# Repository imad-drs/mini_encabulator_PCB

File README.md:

# Mini Encabulator - PCB Design Project

A complete PCB design exercise demonstrating schematic capture, component selection, and board layout using KiCAD. This project implements a simple LED blinker with user-controllable blink rate.

*Final PCB layout with component placement and routing*

## 📋 Project Overview

The Mini Encabulator is a microcontroller-based device that:
- **Blinks an LED** when a button is pressed
- **Controls blink rate** via potentiometer position
- Demonstrates **complete PCB design workflow** from schematic to manufacturing files

This project was designed as a learning exercise for PCB design fundamentals, including proper power delivery, signal conditioning, and mechanical integration with an enclosure.

## 🎯 Features

- **Microcontroller-based control** using ATTiny85
- **Hardware debouncing** for reliable button input
- **Analog input** from potentiometer for variable timing
- **Regulated 5V power supply** from 7-12V input
- **In-circuit programming** via ISP header
- **Enclosure-ready design** with precise mounting holes
- **Two-layer PCB** with ground planes for noise immunity

## 🔧 Hardware Components

### Main Components

| Component | Part Number | Package | Purpose | Quantity |
|-----------|-------------|---------|---------|----------|
| Microcontroller | ATTiny85-20S | SOIC-8 | Main processor | 1 |
| Voltage Regulator | LM1117MP-5.0 | SOT-223 | 5V power supply | 1 |
| Protection Diode | MBR0520 | SOD-123 | Reverse current protection | 1 |

### Passive Components

| Component | Value | Package | Purpose | Quantity |
|-----------|-------|---------|---------|----------|
| Resistor | 10kΩ | 0805 | RESET pull-up | 1 |
| Resistor | 10kΩ | 0805 | Button debounce | 1 |
| Resistor | 1kΩ | 0805 | LED current limit | 1 |
| Capacitor | 1µF | 0805 | Power decoupling | 1 |
| Capacitor | 1µF | 0805 | Button debounce | 1 |

### Connectors

| Connector | Type | Pitch | Purpose | Quantity |
|-----------|------|-------|---------|----------|
| Power Input | Molex KK-254 2-pin | 2.54mm | External power | 1 |
| Button | Molex KK-254 2-pin | 2.54mm | User input | 1 |
| LED | Molex KK-254 2-pin | 2.54mm | Indicator output | 1 |
| Potentiometer | Molex KK-254 3-pin | 2.54mm | Analog input | 1 |
| ISP Header | IDC 2x3 | 2.54mm | Programming interface | 1 |

### Mechanical

- **Mounting Holes**: 4× M3 (3.2mm diameter)
- **Potential Compatible Enclosure**: Polycase SN25 or similar

## 📐 Technical Specifications

### Electrical Characteristics

- **Input Voltage**: 7-12V DC
- **Regulated Output**: 5V @ 800mA max (LM1117)
- **Microcontroller**: 20MHz max, 8KB Flash, 512B SRAM
- **Power Consumption**: ~50mA typical
- **LED Current**: 4mA @ 5V with 1kΩ resistor

### Design Rules

- **Minimum Trace Width**: 10 mil (0.254mm)
- **Power Trace Width**: 20 mil (0.508mm)
- **Minimum Clearance**: 10 mil (0.254mm)
- **Via Size**: 31.5 mil pad / 15.7 mil drill
- **Mounting Hole Spacing**: 1.575" × 1.260" (exact)

## 🔌 Pinout & Connections

### ATTiny85 Pin Assignment

| Pin | Function | Connected To |
|-----|----------|--------------|
| 1 (PB5) | RESET | Pull-up resistor, ISP header |
| 2 (PB3) | Potentiometer | J5 (POT wiper) |
| 3 (PB4) | Button Input | J3 (BUTTON) through RC filter |
| 4 (GND) | Ground | Ground plane |
| 5 (PB0) | MOSI/LED | R4 → J4 (LED) |
| 6 (PB1) | MISO | ISP header |
| 7 (PB2) | SCK | ISP header |
| 8 (VCC) | Power | +5V rail, C1 decoupling |

### External Connections

**J1 (Button)**: Momentary Switch
- Pin 1: Ground
- Pin 2: Switch terminal

**J3 (Vin)**: Power Input
- Pin 1: Ground
- Pin 2: +7-12V DC

**J4 (LED)**: Indicator LED
- Pin 1: Anode (+)
- Pin 2: Cathode (-)

**J5 (Pot)**: Potentiometer (10kΩ recommended)
- Pin 1: +5V
- Pin 2: Wiper (ADC input)
- Pin 3: Ground

## 🛠️ Design Methodology

### Power Distribution

1. **Input Protection**: Reverse polarity protection via Schottky diode
2. **Regulation**: LM1117 drops 7-12V input to stable 5V
3. **Decoupling**: 1µF capacitor near microcontroller VCC pin
4. **Ground Plane**: Solid copper pour on both layers for low impedance return path

### Signal Conditioning

1. **Button Debouncing**: Hardware RC filter (τ = 10ms) eliminates mechanical bounce 
2. **RESET Pull-up**: 10kΩ resistor prevents accidental resets from floating pin 
3. **LED Current Limiting**: 1kΩ resistor limits current to safe 4mA

### Layout Strategy

1. **Component Grouping**: Functional blocks grouped as in schematic
2. **Trace Routing**: 
   - Power traces: 20 mil width
   - Signal traces: 10 mil width
3. **Via Placement**: Ground stitching vias connect top/bottom planes
4. **Clearances**: 10 mil minimum trace-to-trace spacing

## 🤝 Contributing

Contributions are welcome! Please feel free to submit issues or pull requests.

### Areas for Improvement

- [ ] Add firmware source code
- [ ] Create 3D render of assembled board
- [ ] Design custom enclosure (OpenSCAD/FreeCAD)
- [ ] Add test points for debugging
- [ ] Implement sleep mode for power saving
- [ ] Create assembly video tutorial

## 🙏 Acknowledgments

- **KiCAD** - Open-source EDA tool
- **ZJUI ECE 445 / ME 470** - Course structure inspiration
- **Atmel/Microchip** - ATTiny85 datasheet and resources

## 📧 Contact

**Drias Imad Eddine** -  drias.imad2006@gmail.com

---

⭐ **If you found this project helpful, please consider giving it a star!**

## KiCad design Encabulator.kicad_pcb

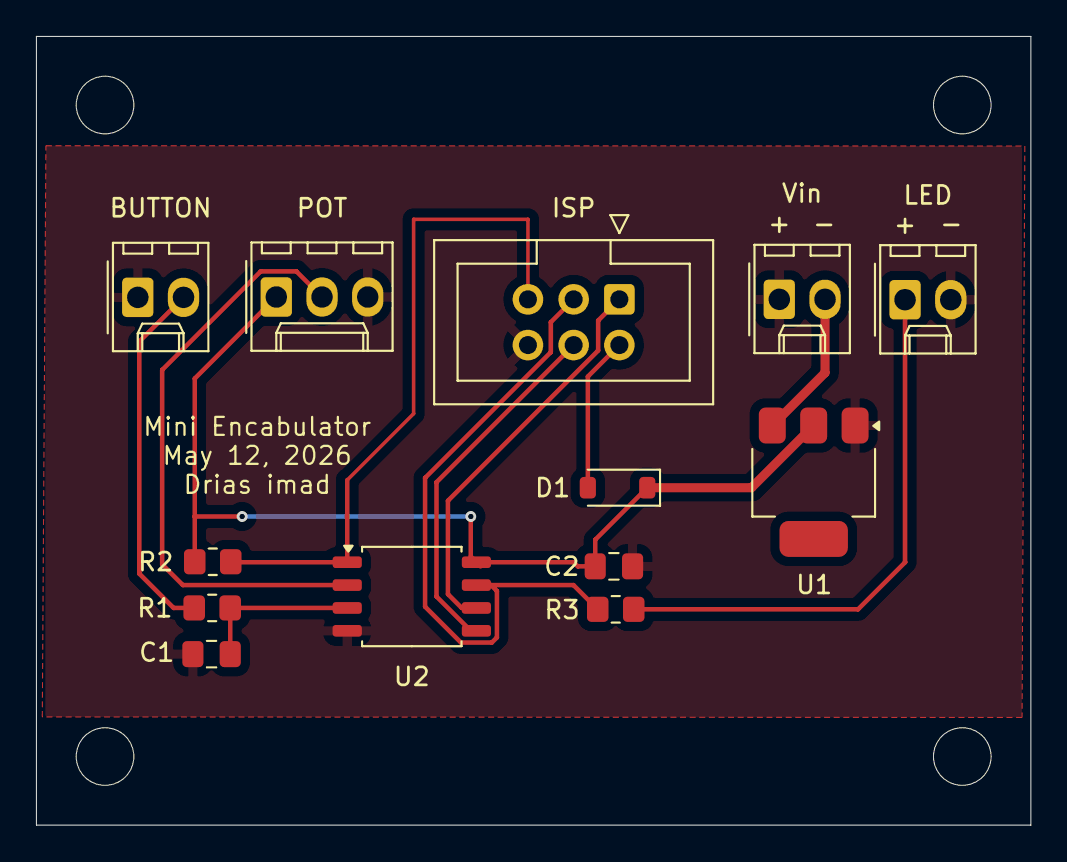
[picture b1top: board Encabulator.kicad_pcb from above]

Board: 2 copper layers, 55.2 x 43.8 mm, 17 parts (0 on the bottom side), 12 nets.

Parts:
C1, C2: 1u; C_0805_2012Metric_Pad1.18x1.45mm_HandSolder
D1: MBR0520; D_SOD-123
H1, H2, H3, H4: MountingHole; MountingHole_3.2mm_M3
ISP: AVR-ISP-6; IDC-Header_2x03_P2.54mm_Vertical
J1: BUTTON; Molex_KK-254_AE-6410-02A_1x02_P2.54mm_Vertical
J3: Vin; Molex_KK-254_AE-6410-02A_1x02_P2.54mm_Vertical
J4: LED; Molex_KK-254_AE-6410-02A_1x02_P2.54mm_Vertical
J5: POT; Molex_KK-254_AE-6410-03A_1x03_P2.54mm_Vertical
R1, R2: 10k; R_0805_2012Metric_Pad1.20x1.40mm_HandSolder
R3: 1k; R_0805_2012Metric_Pad1.20x1.40mm_HandSolder
U1: LM1117MP-5.0; SOT-223
U2: ATtiny85-20S; SOIC-8_5.3x5.3mm_P1.27mm

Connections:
+5V: C2.2, D1.1 (K), J5.1, R2.1, U1.2 (VO), U2.8 (VCC)
/BUTTON: C1.1, R1.2, U2.3 (XTAL2/PB4)
/MISO: ISP.1 (MISO), U2.6 (PB1)
/MOSI: ISP.4 (MOSI), U2.5 (AREF/PB0)
/RST: ISP.5 (~RST), R2.2, U2.1 (~RESET/PB5)
/SCK: ISP.3 (SCK), R3.1, U2.7 (PB2)
GND: C1.2, C2.1, ISP.6 (GND), J1.1, J3.1, J4.2, J5.3, U1.1 (GND), U2.4 (GND)
unnamed: D1.2 (A), ISP.2 (VCC)
unnamed: J1.2, R1.1
unnamed: J3.2, U1.3 (VI)
unnamed: J4.1, R3.2
unnamed: J5.2, U2.2 (XTAL1/PB3)

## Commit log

2026-05-13 Initial upload of the files
2026-05-13 Update README with project details and specifications
    Added detailed project description, features, hardware components, and design methodology for the Mini Encabulator PCB project.
